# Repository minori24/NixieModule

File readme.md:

# nix module: miniature nixie tube driver modules

## nix module(仮)
nix moduleはニキシー管の制御に必要な部品を2x4cmの小さな基板に詰め込んだモジュールです。高圧電源の制御や煩雑なダイナミック点灯のコードを考える必要もなく、マイコンとI2Cで接続するだけでニキシー管の制御が可能です。Arduinoライブラリと組み合わせることでシンプルにニキシー管を点灯させることができます。

最大16桁をI2C経由で連結させ、各桁を独立して制御できます。すべての数字でフェードイン・フェードアウト、シャッフルなどのエフェクトが可能です。またRGB LEDによるバックライトもついています。

## Features
- 2x4cm
- I2Cインタフェース(プルアップ抵抗実装済み)
- ハードウェアPWM制御
- RGBバックライト(WS2812B互換 SK6812mini)
- スタティック点灯でシンプルな回路構成

## Arduino Library
ライブラリは[こちら](https://github.com/minori24/Lib_Nixie_Module)にあります。

使用方法は [Getting Started](doc/getting_started.md) および [Library Reference](doc/library_reference.md) を参照して下さい。

## Open Design
回路図、BOM、PCB DesignをこのGitHub Repoで公開しています。KiCadで自由に編集可能です。

回路図(IN-12 module): [Nixie_Module_IN-12_Schematics.pdf](doc/Nixie_Module_IN-12_Schematics.pdf)

PWMドライバはサーボモータの制御によく使われるPCA9685PW、RGB LEDはシリアル接続LEDの小型版なので、Arduino以外のマイコンボードやRaspberry Piによる制御も簡単に行えます。

## Issue
動作に不明点、問題などある場合はぜひ[Issue](https://github.com/minori24/NixieModule/issues)を立てて下さい。

## Project Examples

Nixie Watch (by [@Robo_akira](https://twitter.com/Robo_akira/status/1117429584108982274))

IN-14 Nixie Clock

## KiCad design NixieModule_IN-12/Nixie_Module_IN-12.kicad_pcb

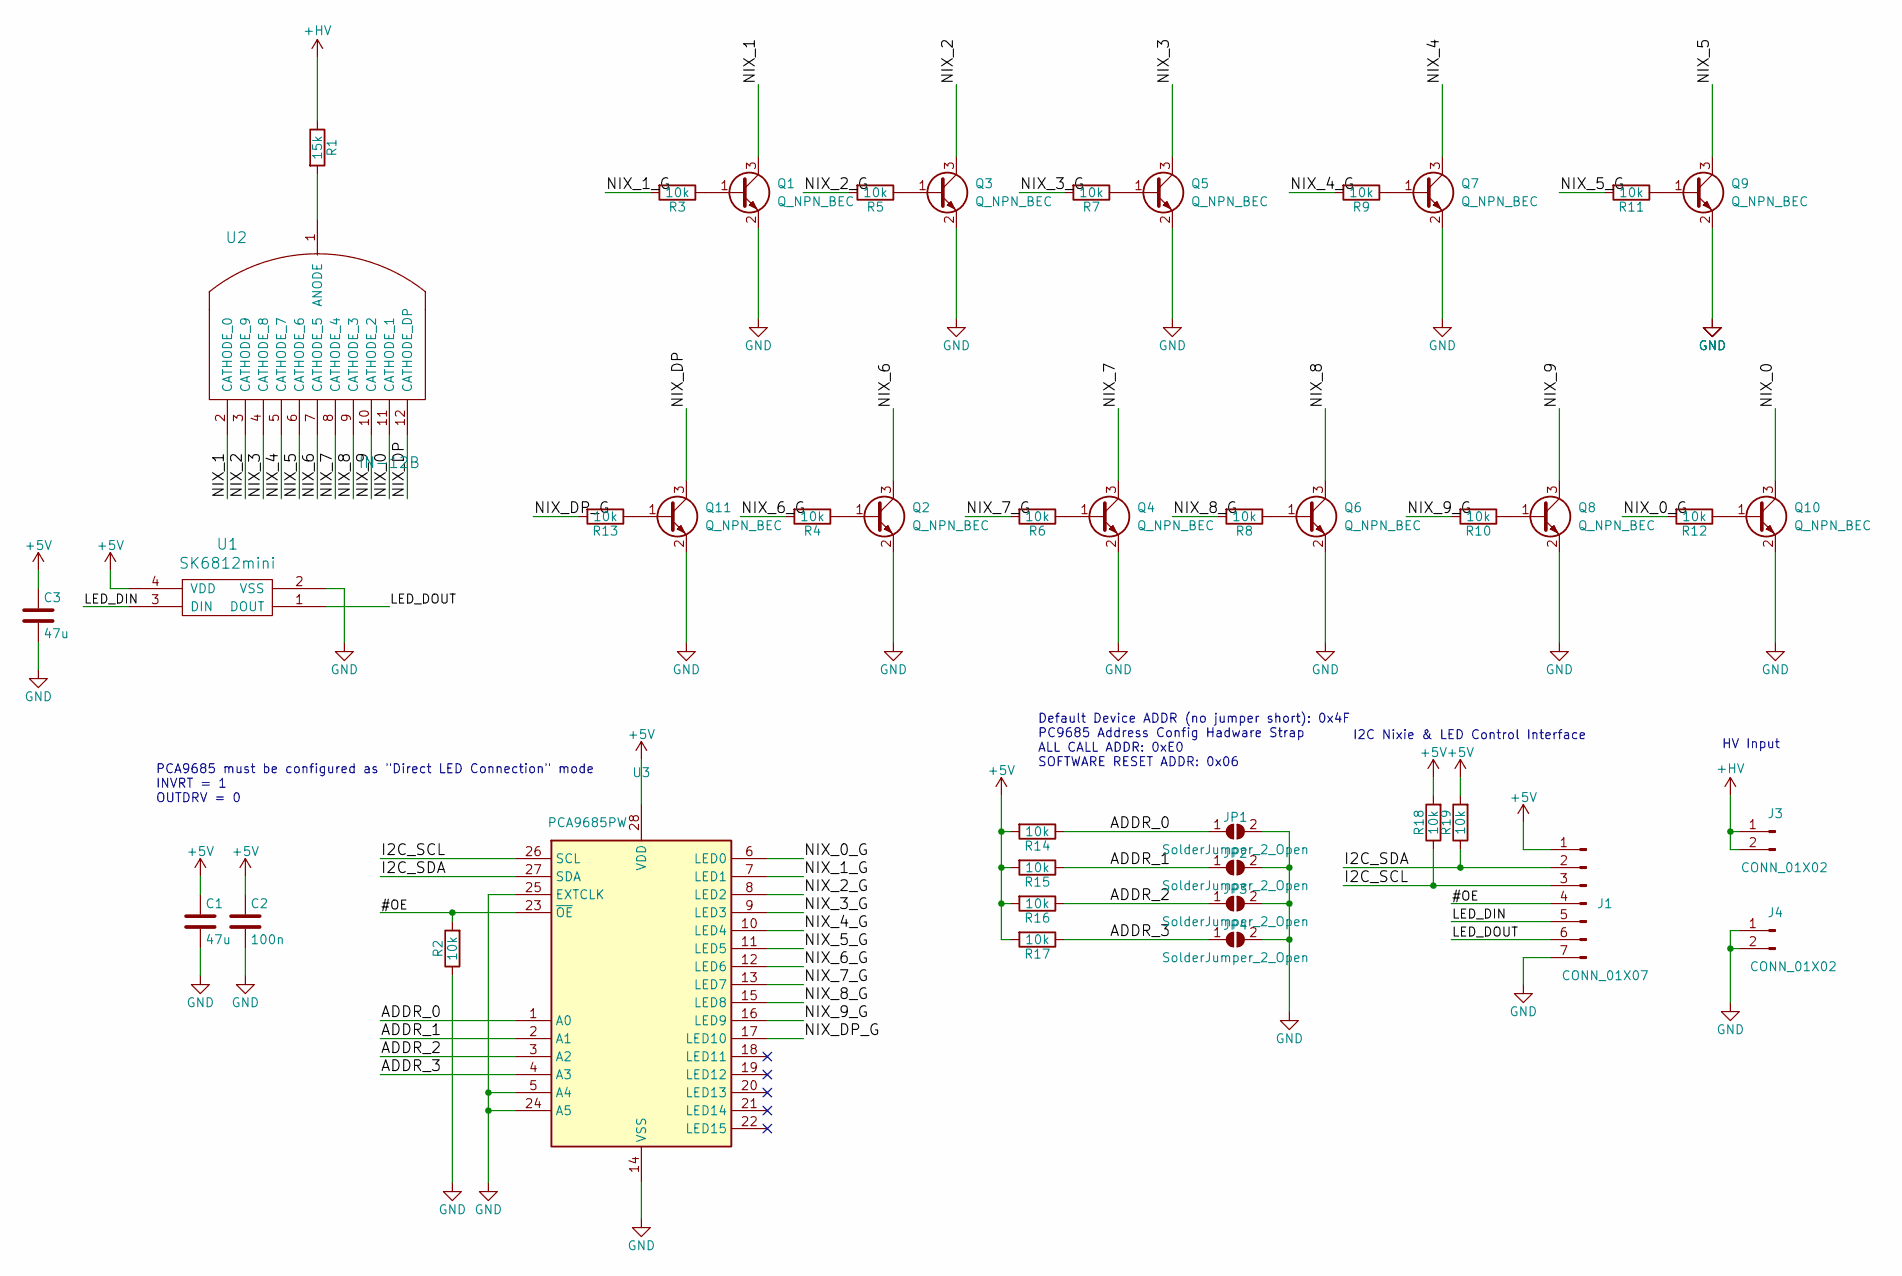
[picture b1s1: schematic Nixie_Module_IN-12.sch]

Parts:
C1, C3: 47u; C_0603
C2: 100n; C_0603
J1: CONN_01X07; Pin_Header_Straight_1x07_Pitch2.54mm
J3, J4: CONN_01X02; Pin_Header_Straight_1x02_Pitch2.54mm
JP1, JP2, JP3, JP4: SolderJumper_2_Open; SolderJumper-2_P1.3mm_Open_RoundedPad1.0x1.5mm
Q1, Q2, Q3, Q4, Q5, Q6, Q7, Q8, Q9, Q10, Q11: Q_NPN_BEC; SOT-23
R1: 15k; R_0603
R2, R3, R4, R5, R6, R7, R8, R9, R10, R11, R12, R13, R14, R15, R16, R17, R18, R19: 10k; R_0603
U1: SK6812mini; SK6812MINI
U2: IN-12B
U3: PCA9685PW; TSSOP-28_4.4x9.7mm_Pitch0.65mm

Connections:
+5V: C1.1, C2.1, C3.1, J1.1, R14.2, R15.2, R16.2, R17.2, R18.2, R19.2, U1.4 (VDD), U3.28 (VDD)
+HV: J3.1, J3.2, R1.1
/#OE: J1.4, R2.2, U3.23 (~OE)
/ADDR_0: JP1.1 (A), R14.1, U3.1 (A0)
/ADDR_1: JP2.1 (A), R15.1, U3.2 (A1)
/ADDR_2: JP3.1 (A), R16.1, U3.3 (A2)
/ADDR_3: JP4.1 (A), R17.1, U3.4 (A3)
/I2C_SCL: J1.3, R18.1, U3.26 (SCL)
/I2C_SDA: J1.2, R19.1, U3.27 (SDA)
/LED_DIN: J1.5, U1.3 (DIN)
/LED_DOUT: J1.6, U1.1 (DOUT)
/NIX_0: Q10.3 (C), U2.11 (CATHODE_1)
/NIX_0_G: R12.2, U3.6 (LED0)
/NIX_1: Q1.3 (C), U2.2 (CATHODE_0)
/NIX_1_G: R3.2, U3.7 (LED1)
/NIX_2: Q3.3 (C), U2.3 (CATHODE_9)
/NIX_2_G: R5.2, U3.8 (LED2)
/NIX_3: Q5.3 (C), U2.4 (CATHODE_8)
/NIX_3_G: R7.2, U3.9 (LED3)
/NIX_4: Q7.3 (C), U2.5 (CATHODE_7)
/NIX_4_G: R9.2, U3.10 (LED4)
/NIX_5: Q9.3 (C), U2.6 (CATHODE_6)
/NIX_5_G: R11.2, U3.11 (LED5)
/NIX_6: Q2.3 (C), U2.7 (CATHODE_5)
/NIX_6_G: R4.2, U3.12 (LED6)
/NIX_7: Q4.3 (C), U2.8 (CATHODE_4)
/NIX_7_G: R6.2, U3.13 (LED7)
/NIX_8: Q6.3 (C), U2.9 (CATHODE_3)
/NIX_8_G: R8.2, U3.15 (LED8)
/NIX_9: Q8.3 (C), U2.10 (CATHODE_2)
/NIX_9_G: R10.2, U3.16 (LED9)
/NIX_DP: Q11.3 (C), U2.12 (CATHODE_DP)
/NIX_DP_G: R13.2, U3.17 (LED10)
GND: C1.2, C2.2, C3.2, J1.7, J4.1, J4.2, JP1.2 (B), JP2.2 (B), JP3.2 (B), JP4.2 (B), Q1.2 (E), Q2.2 (E), Q3.2 (E), Q4.2 (E), Q5.2 (E), Q6.2 (E), Q7.2 (E), Q8.2 (E), Q9.2 (E), Q10.2 (E), Q11.2 (E), R2.1, U1.2 (VSS), U3.5 (A4), U3.14 (VSS), U3.24 (A5), U3.25 (EXTCLK)
unnamed: Q1.1 (B), R3.1
unnamed: Q2.1 (B), R4.1
unnamed: Q3.1 (B), R5.1
unnamed: Q4.1 (B), R6.1
unnamed: Q5.1 (B), R7.1
unnamed: Q6.1 (B), R8.1
unnamed: Q7.1 (B), R9.1
unnamed: Q8.1 (B), R10.1
unnamed: Q9.1 (B), R11.1
unnamed: Q10.1 (B), R12.1
unnamed: Q11.1 (B), R13.1
unnamed: R1.2, U2.1 (ANODE)

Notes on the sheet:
Default Device ADDR (no jumper short): 0x4F PC9685 Address Config Hadware Strap ALL CALL ADDR: 0xE0 SOFTWARE RESET ADDR: 0x06
PCA9685 must be configured as "Direct LED Connection" mode INVRT = 1 OUTDRV = 0
I2C Nixie & LED Control Interface
HV Input

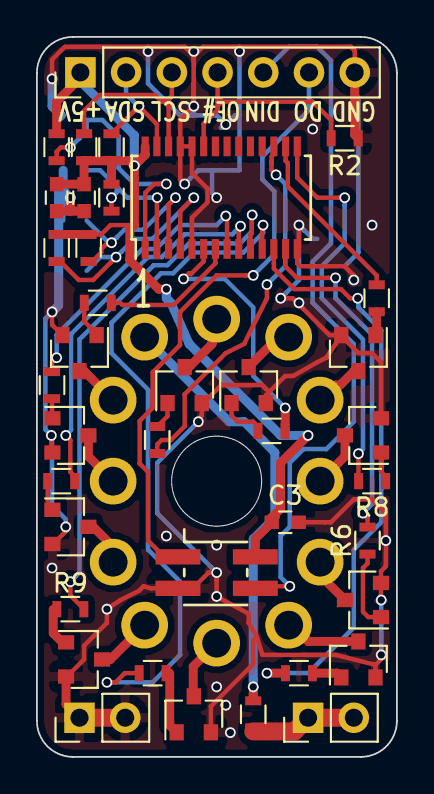
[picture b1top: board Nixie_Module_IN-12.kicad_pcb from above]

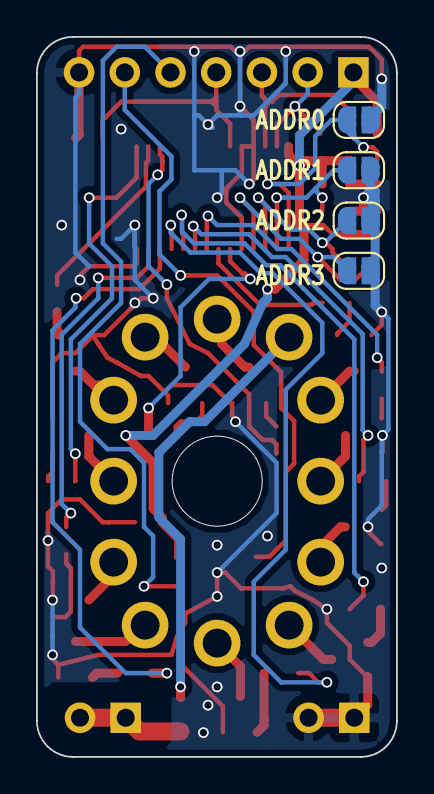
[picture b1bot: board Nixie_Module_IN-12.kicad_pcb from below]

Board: 2 copper layers, 20.0 x 40.0 mm, 43 parts (4 on the bottom side), 46 nets.

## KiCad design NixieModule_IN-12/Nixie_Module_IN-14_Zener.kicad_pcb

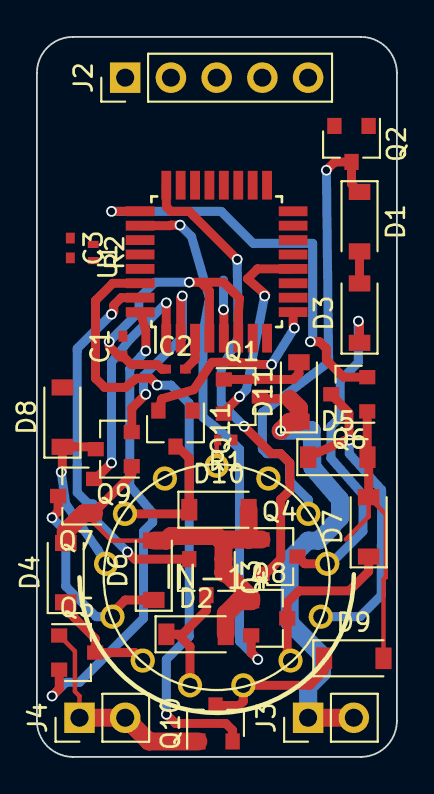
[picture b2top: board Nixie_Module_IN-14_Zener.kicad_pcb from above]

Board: 2 copper layers, 20.0 x 40.0 mm, 33 parts (1 on the bottom side), 34 nets.

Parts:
C1: 47u; C_0402_NoSilk
C2, C3: 100n; C_0402_NoSilk
D1, D2, D3, D4, D5, D6, D7, D8, D9, D10, D11: D_Zener; D_SOD-123
J1: CONN_01X04; PinHead_SMD_1x4
J2: CONN_01X05; Pin_Header_Straight_1x05_Pitch2.54mm
J3, J4: CONN_01X02; Pin_Header_Straight_1x02_Pitch2.54mm
N1: IN-14; russian-nixies-IN-14
Q1, Q2, Q3, Q4, Q5, Q6, Q7, Q8, Q9, Q10, Q11: Q_NMOS_SGD; SOT-23
R1, R2: R; R_0402_NoSilk
U1: ATMEGA48-20AU; TQFP-32_7x7mm_Pitch0.8mm

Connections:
+5V: C1.1, C2.1, J2.1, R2.1, U1.4, U1.6, U1.18
+HV: D11.1, J3.1, J3.2, Q1.3
/#RESET: C3.2, R2.2, U1.29
/I2C_SCL: J2.4, U1.28
/I2C_SDA: J2.3, U1.27
/NIX_0: D10.1, N1.0, Q11.3
/NIX_0_G: Q11.2, U1.9
/NIX_1: D1.1, N1.1, Q2.3
/NIX_1_G: Q2.2, U1.23
/NIX_2: D3.1, N1.2, Q4.3
/NIX_2_G: Q4.2, U1.24
/NIX_3: D5.1, N1.3, Q6.3
/NIX_3_G: Q6.2, U1.25
/NIX_4: D7.1, N1.4, Q8.3
/NIX_4_G: Q8.2, U1.26
/NIX_5: D9.1, N1.5, Q10.3
/NIX_5_G: Q10.2, U1.30
/NIX_6: D2.1, N1.6, Q3.3
/NIX_6_G: Q3.2, U1.31
/NIX_7: D4.1, N1.7, Q5.3
/NIX_7_G: Q5.2, U1.32
/NIX_8: D6.1, N1.8, Q7.3
/NIX_8_G: Q7.2, U1.1
/NIX_9: D8.1, N1.9, Q9.3
/NIX_9_G: Q9.2, U1.2
/NIX_ANODE: Q1.2, U1.12
/SPI_#SS: J1.1, U1.14
/SPI_MISO: J1.3, U1.16
/SPI_MOSI: J1.2, U1.15
/SPI_SCK: J1.4, U1.17
GND: C1.2, C2.2, D1.2, D2.2, D3.2, D4.2, D5.2, D6.2, D7.2, D8.2, D9.2, D10.2, J2.5, J4.1, J4.2, Q2.1, Q3.1, Q4.1, Q5.1, Q6.1, Q7.1, Q8.1, Q9.1, Q10.1, Q11.1, U1.3, U1.5, U1.21
unnamed: C3.1, J2.2
unnamed: D11.2, Q1.1, R1.1
unnamed: N1.A, R1.2

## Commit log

2019-02-04 fix link
2019-02-05 Update documentation
2019-02-09 update manual
2019-03-02 correct code in document
2019-04-15 update document
2020-02-14 Document update
